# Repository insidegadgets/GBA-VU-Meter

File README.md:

# GBA-VU-Meter
Add a VU Meter to your GBA

License: CC-BY-NC

The ATtiny48 part number to order is any of these:
ATTINY48-MMU
ATTINY48-MMUR
ATtiny48-MMH
ATtiny48-MMHR

You can play around with the 0.1uF / 10K resistor and the startCompare value.

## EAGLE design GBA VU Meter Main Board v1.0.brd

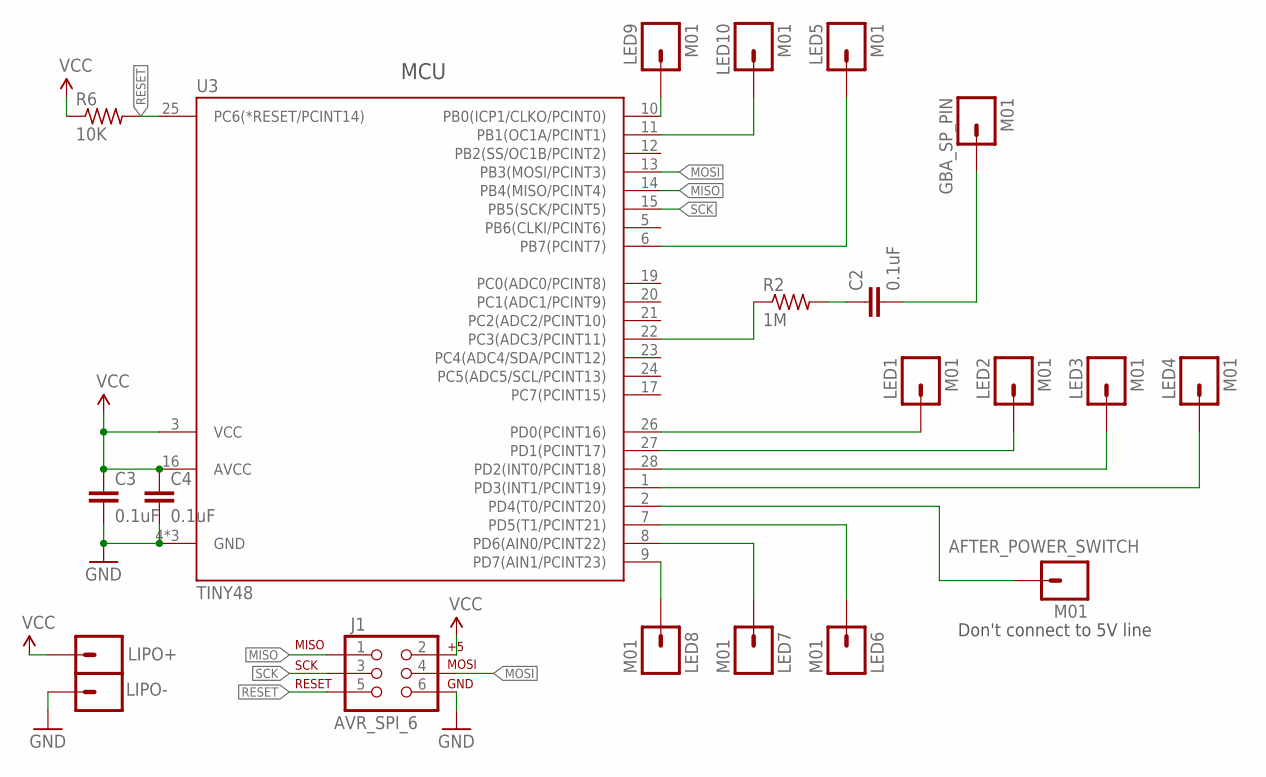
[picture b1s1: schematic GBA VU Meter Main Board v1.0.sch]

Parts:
AFTER_POWER_SWITCH: M01; 1X01_SMD_SM
C2, C3, C4: 0.1uF; C0603K
GBA_SP_PIN: M01; 1X01_SMD_SM
J1: AVR_SPI_6; 2X3_2
LED1, LED2, LED3, LED4, LED5, LED6, LED7, LED8, LED9, LED10: M01; 1X01_SMD_SM
LIPO+: M01SMALL; 1X01_SMD_SMALL
LIPO-: M01SMALL; 1X01_SMD_SMALL
R2: 1M; R0603_S
R6: 10K; R0603_S
U3: TINY48; VQFN-28

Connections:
GND: C3.2, C4.2, J1.6, LIPO-.1, U3.4 (GND), U3.18 (GND), U3.29 (GND)
MISO: J1.1, U3.14 (PB4(MISO/PCINT4))
MOSI: J1.4, U3.13 (PB3(MOSI/PCINT3))
unnamed: LED1.P$1, U3.26 (PD0(PCINT16))
unnamed: LED2.P$1, U3.27 (PD1(PCINT17))
unnamed: R2.1, U3.22 (PC3(ADC3/PCINT11))
unnamed: C2.1, R2.2
unnamed: LED4.P$1, U3.1 (PD3(INT1/PCINT19))
unnamed: LED5.P$1, U3.6 (PB7(PCINT7))
unnamed: LED3.P$1, U3.28 (PD2(INT0/PCINT18))
unnamed: AFTER_POWER_SWITCH.P$1, U3.2 (PD4(T0/PCINT20))
unnamed: LED9.P$1, U3.10 (PB0(ICP1/CLKO/PCINT0))
unnamed: LED10.P$1, U3.11 (PB1(OC1A/PCINT1))
unnamed: C2.2, GBA_SP_PIN.P$1
unnamed: LED6.P$1, U3.7 (PD5(T1/PCINT21))
unnamed: LED7.P$1, U3.8 (PD6(AIN0/PCINT22))
unnamed: LED8.P$1, U3.9 (PD7(AIN1/PCINT23))
RESET: J1.5, R6.2, U3.25 (PC6(*RESET/PCINT14))
SCK: J1.3, U3.15 (PB5(SCK/PCINT5))
VCC: C3.1, C4.1, J1.2, LIPO+.1, R6.1, U3.3 (VCC), U3.16 (AVCC)

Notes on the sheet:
MCU
Don't connect to 5V line

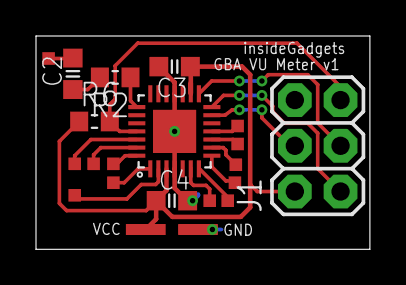
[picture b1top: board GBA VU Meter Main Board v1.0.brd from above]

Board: 2 copper layers, 18.5 x 11.9 mm, 21 parts (0 on the bottom side), 20 nets.

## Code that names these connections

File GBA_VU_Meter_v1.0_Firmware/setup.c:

/*
 GBA VU Meter
 Version: 1.0
 Author: Alex from insideGadgets (http://www.insidegadgets.com)
 Created: 17/03/2020
 Last Modified: 17/03/2020

 */
 
#ifndef cbi
#define cbi(sfr, bit) (_SFR_BYTE(sfr) &= ~_BV(bit))
#endif
#ifndef sbi
#define sbi(sfr, bit) (_SFR_BYTE(sfr) |= _BV(bit))
#endif

#ifndef NULL
#define NULL ((void *)0)
#endif

#define LOW 0
#define HIGH 1
#define false 0
#define true 1

// Watchdog timeouts to values
#define T16MS 0
#define T32MS 1
#define T64MS 2
#define T128MS 3
#define T250MS 4
#define T500MS 5
#define T1S 6
#define T2S 7
#define T4S 8
#define T8S 9

#define ADCPin 3
#define LED1 PD0
#define LED2 PD1
#define LED3 PD2
#define LED4 PD3
#define LED5 PB7
#define LED6 PD5
#define LED7 PD6
#define LED8 PD7
#define LED9 PB0
#define LED10 PB1

// ADC Refs
#define REF_1_1V 0
#define REF_AVCC 1

#define DELAY_TIME 50

// Sleep
void system_sleep(void) {
	set_sleep_mode(SLEEP_MODE_PWR_DOWN); // Set sleep mode
	sleep_mode(); // System sleeps here
}

// Setup watchdog timed sequence
void setup_watchdog(uint8_t wdDelay) {
	if (wdDelay > 9) { 
		wdDelay = 9;
	}
	
	uint8_t bb = wdDelay & 7;
	if (wdDelay > 7) { 
		bb |= (1<<5);
	}
	
	cli(); // Turn interrupts off
	asm("WDR");
	
	MCUSR &= ~(1<<WDRF);
	// Start timed sequence
	WDTCSR |= (1<<WDCE) | (1<<WDE);
	// Set new watchdog timeout value
	WDTCSR = bb | (1<<WDIE);
	
	sei(); // Turn interrupts back on
}

// Turn off the Watchdog
void turn_off_watchdog(void) {
	cli(); // Turn interrupts off
	asm("WDR");
	MCUSR &= ~(1<<WDRF);
	WDTCSR |= (1<<WDCE) | (1<<WDIE);
	WDTCSR = 0;
	sei(); // Turn interrupts back on
}

// Watchdog sleep function - setup, sleep and turn off
void watchdog_sleep(uint8_t timeout) { 
	setup_watchdog(timeout);
	system_sleep();
	turn_off_watchdog();
}

// Read the ADC
int adc_read(uint8_t pin, uint8_t reference) {
	uint8_t low, high;
	
	// Set the analog reference (high two bits of ADMUX) and select the channel (low 4 bits)
	if (reference == REF_1_1V) {
		ADMUX = (pin & 0x0F); // 1.1V reference
	}
	else {
		ADMUX = (1<<REFS0) | (pin & 0x0F); // AVCC Ref
	}
	
	set_sleep_mode(SLEEP_MODE_ADC); // Set sleep mode ADC
	sleep_mode(); // System sleeps here
	
	// Read ADCL first
	low = ADCL;
	high = ADCH;
	
	// combine the two bytes
	return (high << 8) | low;
}
// Setup
void setup(void) {
	// Turn on pull ups
	PORTB |= (1<<PB2) | (1<<PB3) | (1<<PB4) | (1<<PB5) | (1<<PB6); 
	PORTC |= (1<<PC0) | (1<<PC1) | (1<<PC2) | (1<<PC4) | (1<<PC5) | (1<<PC6) | (1<<PC7); 
	
	// Setup outputs
	DDRD |= (1<<LED1) | (1<<LED2) | (1<<LED3) | (1<<LED4) | (1<<LED6) | (1<<LED7) | (1<<LED8);
	DDRB |= (1<<LED5)  | (1<<LED9) | (1<<LED10);
	
	// Set ADC prescale factor to 8
	// 1 MHz / 8 = 125 KHz, inside the desired 50-200 KHz range.
	sbi(ADCSRA, ADPS1);
	sbi(ADCSRA, ADPS0);
	
	// Enable ADC/interrupt
	sbi(ADCSRA, ADEN);
	sbi(ADCSRA, ADIE);
	
	// Blink LEDs
	//PORTD |= (1<<LED1) | (1<<LED2) | (1<<LED3) | (1<<LED4) | (1<<LED6) | (1<<LED7) | (1<<LED8);
	//PORTB |= (1<<LED5) | (1<<LED9) | (1<<LED10);
	//_delay_ms(200);
	//PORTD &= ~((1<<LED1) | (1<<LED2) | (1<<LED3) | (1<<LED4) | (1<<LED6) | (1<<LED7) | (1<<LED8));
	//PORTB &= ~((1<<LED5) | (1<<LED9) | (1<<LED10));
	
	sei(); // Turn on interrupts
}

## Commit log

2020-03-17 Added firmware and PCB
